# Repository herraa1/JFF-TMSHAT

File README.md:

# JFF Computer with TMSHAT

This is an enhanced version of the [JFF Computer](https://github.com/konkotgit/JFF) by @Skoti, which enables the use of the TMS9928A or TMS9929A Video Display Processors (VDPs), in addition to the TMS9918A VDP.

## Current Status

:white_check_mark: Completed!

The modified JFF mainboard 1.1b-TMSHAT Build1 has been successfully designed, built and tested (as of Aug 20th, 2025). See *warning* on the next paragraph.

The TMSRGBCustom TMSHAT Build1 has been successfully designed, built and tested (as of Sep 11th, 2025). It has been successfully tested for RGB output on the modified JFF mainboard 1.1b-TMSHAT Build1 with both a TMS9929A NL (50Hz) and a TMS9928AN (60Hz).

The TMSRGBv2 TMSHAT Build1 has been successfully designed, built and tested (as of Oct 11th, 2025). It has been successfully tested for RGB output on the modified JFF mainboard 1.1b-TMSHAT Build1 with a TMS9928AN (60Hz) and a TMS9929A NL (50Hz).

> [!WARNING]
>
> While building the JFF mainboard it has been detected that the original JFF mainboard revision 1.1b has a bug in the general purpose IO ports schematic similar (but different) to [the bug that affected the Omega Home Computer prior to version 1.5](https://github.com/skiselev/omega/issues/56) which the modified JFF mainboard revision 1.1b-TMSHAT Build1 has *inherited*. The bug does not affect MSX joysticks, only IO devices which require output to the trigger pins are affected.
>
> For existing original JFF revision 1.1b mainboards (and for the modified JFF mainboard revision 1.1b-TMSHAT Build1), the [JFF joyfix board](https://github.com/herraa1/JFF-1.1-joyfix-board-v1) interposer board has been developed to fix the joystick circuit problem, and has been already validated (as of Oct 3rd, 2025).
>
> A [new revision 1.1c](https://github.com/konkotgit/JFF?tab=readme-ov-file#revisions) of the original JFF mainboard that fixes the joystick circuit bug has been published by @Skoti (as of Oct 6th, 2025) solving [Issue #3](https://github.com/konkotgit/JFF/issues/3).
>
> And the equivalent [JFF-TMSHAT Mainboard revision 1.1c-TMSHAT](https://github.com/herraa1/JFF-TMSHAT/tree/main/hardware/kicad/JFF-TMSHAT-Mainboard-Build1/jff_mainboard-1.1c-TMSHAT) has been released by @herraa1 (as of Oct 6th, 2025), but has not been built nor tested.
>

> [!NOTE]
>
> Everything stated here about revision 1.1b-TMSHAT is applicable to 1.1c-TMSHAT. The only difference between the two board revisions is the fix for the joystick circuit bug.

## Sponsorship

.

The fabrication of the *Build1* mainboard 1.1b-TMSHAT, Hat-TMSRGBv2 and Hat-TMSRGBCustom PCB prototypes has been kindly sponsored by [PCBWay](https://www.pcbway.com), a global quality-focused PCB manufacturer which provides [sponsorship](https://www.kicad.org/sponsors/sponsors/) for the [KiCad project](https://www.kicad.org) as well as many educational and [open source hardware](https://en.wikipedia.org/wiki/Open-source_hardware) projects.

KiCad is the open source [EDA](https://en.wikipedia.org/wiki/Electronic_design_automation) platform of choice used to design the hardware circuitry provided in the JFF-TMSHAT project.

## Motivation

The JFF Computer by @Skoti is a [MSX1 compatible computer](https://www.msx.org/wiki/MSX1) which uses the TMS9918A VDP which is part of the [TMS9918 family](https://en.wikipedia.org/wiki/TMS9918) of Video Display Processors from Texas Instruments.
The TMS9918A outputs a 60Hz composite NTSC video signal, and thus the JFF has a single RCA video output connector with a composite video signal.

The TMS9928A and TMS9929A VDPs, from the same family of Video Display Processors, output instead analog luminance (Y) and color difference (R-Y and B-Y) signals.
Except for the video output signals, the TMS9918A, TMS9928A and TMS9929A VDPs behave identically and have an almost identical pinout.

The difference in the pinout of the TMS9918A, TMS9928A and TMS9929A VDPs affects the following pins:

| **Pin Number** | **TMS9918A Name** | **TMS9918A Description**        | **TMS9928A/TMS9929A Name** | **TMS9928A/TMS9929A Description** |
| -------------- | ----------------- | ------------------------------- | -------------------------- | --------------------------------- |
| 35             | EXTVDP            | External VDP input              | B-Y                        | B-Y color difference output       |
| 36             | COMVID            | Composite video output          | Y                          | luminance/sync output             |
| 38             | CPUCLK            | VDP color burst frequency clock | R-Y                        | R-Y color difference output       |

Given that the JFF Computer does not use VDP pins 35 nor 38, and just uses pin 36 for composite video output, it should be relatively straightforward to allow the use of the TMS9928A or TMS9929A VDPs alternatively to the TMS9918A VDP.
Using the luminance and color difference signals provided by the TMS9928A or TMS9929A VDPs, an enhanced output video signal like RGB or component video can be generated for a better user experience.

## Proposed Changes

### Original JFF Computer mainboard (rev 1.1b)

### Modified JFF Computer mainboard (rev 1.1b-TMSHAT)

The JFF computer mainboard is modified as described here.

* A new audio/video header J13 is added to the JFF computer mainboard, which can be used to select between the TMS9918A or TMS9928A/TMS9929A VDPs, and to provide the required audio and video signals to an external companion card called TMSHAT which converts them into a specific audio/video output.

  The header provides access to the following signals:

  | **Pin Number** | **Name**   | **Type<br>(from JFF connector point of view)** | **Function**                                              |
  | -------------- | ---------- | ---------------------------------------------- | --------------------------------------------------------- |
  | 1              | GND        | Power                                          | Common ground                                             |
  | 2              | +5V        | Power                                          | 5V power rail                                             |
  | 3              | CPUCLK/R-Y | OUT                                            | direct signal from pin 38 of VDP                          |
  | 4              | EXTVDP/B-Y | OUT                                            | direct signal from pin 35 of VDP                          |
  | 5              | COMVID/Y   | OUT                                            | direct signal from pin 36 of VDP                          |
  | 6              | COMVID_OUT | IN                                             | connected to JFF mainboard composite video output circuit |
  | 7              | NC         |                                                | (reserved)                                                |
  | 8              | AUDIO      | OUT                                            | final mixed audio signal                                  |

  A total of 8 pins are used for the audio/video header, giving 1 extra pin for future use.

  Allowed VDP configurations:

  - *TMS9918A*

    To use a TMS9918A VDP, pins 5 (COMVID/Y) and 6 (COMVID_OUT) of J13, which use inverted colors in the silkscreen text, must be bridged and a TMS9918A must be installed in U6.
    In this configuration the modified JFF computer works identically as the original JFF computer with a TMS9918A and outputs a composite video signal on the motherboard video RCA connector.

  - *TMS9928A/TMS9929A*

    To use a TMS9928A or TMS9929A VDP, a companion TMSHAT card needs to be connected to J13 and a TMS9928A or TMS9929A VDP must be installed in U6.
    In this configuration the modified JFF computer will provide an audio and video output according to the capabilities of the TMSHAT card connected.
    
* A small clearance area is defined between the power barrel connector and the DIN8 cassette connector in the JFF computer mainboard.

  This allows to, as long as they fit, seamlessly place in that area the additional audio/video connectors provided by the TMSHAT cards.
  Note that the additional audio/video connectors are never part of the JFF computer mainboard, they are instead soldered to the TMSHAT cards. But, for convenience, the mentioned area allows making such connectors available on the back of the JFF computer as if they were on the mainboard.

  The power led is relocated next to the Audio connector in the JFF computer motherboard to allow the described clearance.

* Enough clearance is preserved too for the DD1718PA +12V/-12V voltage module converter to be installed upside-down in the J5 header.

* A new extra 3mm hole is added to the JFF computer mainboard.

  A TMSHAT card must be properly attached to the JFF computer mainboard, specially as it has to deal with cable insertion/removal forces when audio/video connectors are present on the TMSHAT card itself.

  The top-left 3mm hole and the new 3mm hole on the JFF computer mainboard are the mechanical attachment points for the TMSHAT cards, while the audio/video header attachment provides the electrical signals.

* External companion TMSHAT cards are designed to be connected to the new audio/video header J13, attached to the previously described mainboard holes and shaped to avoid any collision with existing components in the JFF computer. The TMSHAT cards provide a specific audio/video output using one or more embedded connectors in the card itself.

  As an example, a pair of TMSHAT card implementations are provided to convert the luminance and color difference signals of the TMS9928A and TMS9929A VDPs to RGB, and output both the audio and RGB video signals through a DIN8 connector compatible with [audio/video cables for Panasonic MSX2+ machines](https://www.msx.org/wiki/RGB_(8-pin_DIN_45326)#Mitsubishi_.28Japan.29.2C_National.2FPanasonic_.28except_the_FS-A1WSX.29.2C_Sakhr.2C_Sony_and_Yamaha_computers_.2B_Sanyo_MSX2.2F2.2B_computers).

## [Hardware](hardware/kicad/)

This project provides source files for the following hardware designs:

* JFF mainboard revisions 1.1b-TMSHAT and 1.1c-TMSHAT aka [JFF-TMSHAT-Mainboard](#jff-tmshat-mainboard)

* TMSHAT for RGB output using a standard TMS-RGBv2 module, aka [JFF-TMSHAT-Hat-TMSRGBv2](#jff-tmshat-hat-tmsrgbv2)

* TMSHAT for RGB output using a custom TMS-RGB implementation, aka [JFF-TMSHAT-Hat-TMSRGBCustom](#jff-tmshat-hat-tmsrgbcustom)

### JFF-TMSHAT-Mainboard

This mainboard design allows using a TMS9928A or TMS9929A VDP in combination with a TMSHAT, or a TMS9918A VDP by just closing a jumper.

#### [JFF-TMSHAT-Mainboard Build1](hardware/kicad/JFF-TMSHAT-Mainboard-Build1/)

:white_check_mark: Revision 1.1b-TMSHAT of this board has been successfully built and tested.

* [Bill Of Materials (BoM)](https://html-preview.github.io/?url=https://raw.githubusercontent.com/herraa1/JFF-TMSHAT/main/hardware/kicad/JFF-TMSHAT-Mainboard-Build1/jff_mainboard-1.1b-TMSHAT/bom/ibom.html)

* [Schematic and PCB](https://kicanvas.org/?github=https%3A%2F%2Fgithub.com%2Fherraa1%2FJFF-TMSHAT%2Ftree%2Fmain%2Fhardware%2Fkicad%2FJFF-TMSHAT-Mainboard-Build1%2Fjff_mainboard-1.1b-TMSHAT)

|||
|-|-|
|JFF mainboard 1.1b-TMSHAT Build1<br>PCB unpopulated top|JFF mainboard 1.1b-TMSHAT Build1<br>PCB unpopulated bottom|

||
|:--|
|JFF mainboard 1.1b-TMSHAT Build1 PCB populated top,<br>with a TMSRGBCustom TMSHAT Build1 connected|

##### Configuration Options

This section provides visual details on how to configure the JFF mainboard 1.1b-TMSHAT for different VDPs.

###### Using a TMS9918A VDP

* Insert a TMS9918ANL into U6
* Use a jumper to bridge pins 5 and 6 of J13
* Connect a composite display to the RCA video connector of the JFF mainboard

###### Using a TMS9928A/TMS9929A VDP with the TMSRGB TMSHATs

* Insert a TMS9928AN/TMS9929ANL into U6
* Remove all jumpers from J13, if any
* Install two 20mm long vertical aluminum round posts on the JFF mainboard holes dedicated for TMSHATs

* Insert the TMSHAT by connecting it to the J13 header and using two M3 screws to secure it to the vertical round posts.

* Connect a 15KHz RGBS display (or a 15KHz video converter suitable for your modern display, like the [OSSC](https://junkerhq.net/xrgb/index.php/OSSC)) to the [Panasonic-compatible DIN8 video connector](https://www.msx.org/wiki/RGB_(8-pin_DIN_45326)#Mitsubishi_.28Japan.29.2C_National.2FPanasonic_.28except_the_FS-A1WSX.29.2C_Sakhr.2C_Sony_and_Yamaha_computers_.2B_Sanyo_MSX2.2F2.2B_computers) of the TMSHAT

  |||
  |-|-|
  |TMS9929A (50Hz) with a TMSRGBCustom TMSHAT|TMS9928A (60Hz) with a TMSRGBCustom TMSHAT|

### JFF-TMSHAT-Hat-TMSRGBv2

This TMSHAT provides RGB output via a DIN8 connector compatible with audio/video cables for Panasonic MSX2+ machines when using a TMS9928A or TMS9929A VDP.

It requires a [TMS-RGB v2 module](https://tms-rgb.com/) by [Nicholas Piegdon](https://twitter.com/npiegdon).

#### [JFF-TMSHAT-Hat-TMSRGBv2 Build1](hardware/kicad/JFF-TMSHAT-Hat-TMSRGBv2-Build1/)

:white_check_mark: This board has been successfully built and tested.

[Bill Of Materials (BoM)](https://html-preview.github.io/?url=https://raw.githubusercontent.com/herraa1/JFF-TMSHAT/main/hardware/kicad/JFF-TMSHAT-Hat-TMSRGBv2-Build1/bom/ibom.html)

[Schematic and PCB](https://kicanvas.org/?github=https%3A%2F%2Fgithub.com%2Fherraa1%2FJFF-TMSHAT%2Ftree%2Fmain%2Fhardware%2Fkicad%2FJFF-TMSHAT-Hat-TMSRGBv2-Build1)

|||
|-|-|
|TMSRGBv2 TMSHAT Build1<br>PCB unpopulated top|TMSRGBv2 TMSHAT Build1<br>PCB unpopulated bottom|

||
|:--|
|TMSRGBv2 TMSHAT Build1 PCB populated top with TMSRGBv2 connected|

||
|:--|
|TMSRGBv2 TMSHAT Build1 PCB populated bottom with TMSRGBv2 connected|

### JFF-TMSHAT-Hat-TMSRGBCustom

This TMSHAT provides RGB output via a DIN8 connector compatible with audio/video cables for Panasonic MSX2+ machines when using a TMS9928A or TMS9929A VDP.

It implements a custom TMS-RGB directly in the TMSHAT.

#### [JFF-TMSHAT-Hat-TMSRGBCustom-Build1](hardware/kicad/JFF-TMSHAT-Hat-TMSRGBCustom-Build1/)

:white_check_mark: This board has been successfully built and tested.

[Bill Of Materials (BoM)](https://html-preview.github.io/?url=https://raw.githubusercontent.com/herraa1/JFF-TMSHAT/main/hardware/kicad/JFF-TMSHAT-Hat-TMSRGBCustom-Build1/bom/ibom.html)

[Schematic and PCB](https://kicanvas.org/?github=https%3A%2F%2Fgithub.com%2Fherraa1%2FJFF-TMSHAT%2Ftree%2Fmain%2Fhardware%2Fkicad%2FJFF-TMSHAT-Hat-TMSRGBCustom-Build1)

|
|-|-|
|TMSRGBCustom TMSHAT Build1<br>PCB unpopulated top|TMSRGBCustom TMSHAT Build1<br>PCB unpopulated bottom|

||
|:--|
|TMSRGBCustom TMSHAT Build1 PCB populated top|

||
|:--|
|TMSRGBCustom TMSHAT Build1 PCB populated bottom (I)|

|
|-|-|
|TMSRGBCustom TMSHAT Build1<br>PCB populated bottom (II)|TMSRGBCustom TMSHAT Build1<br>PCB populated bottom (III)|

## Compatibility tests

| **Motherboard**          | **VDP**     | **TMSHAT**          | **Video Output** | **Result**     |
| ------------------------ | ----------- | ------------------- | ---------------- | -------------- |
| rev 1.1b-TMSHAT Build1   | TMS9918ANL  | None (bridge 5&6)   | Composite 60Hz   | OK             |
| rev 1.1b-TMSHAT Build1   | TMS9928AN   | TMSRGBCustom Build1 | RGBS 60Hz        | OK             |
| rev 1.1b-TMSHAT Build1   | TMS9929ANL  | TMSRGBCustom Build1 | RGBS 50Hz        | OK             |
| rev 1.1b-TMSHAT Build1   | TMS9928AN   | TMSRGBv2 Build1     | RGBS 60Hz        | OK             |
| rev 1.1b-TMSHAT Build1   | TMS9929ANL  | TMSRGBv2 Build1     | RGBS 50Hz        | OK             |

## Design considerations

* The external connectors in the mainboard of the original JFF computer must not be relocated
* Modifications to the original JFF computer must be kept to the minimum necessary to achieve the functional goals
* The modified JFF-TMSHAT computer must behave exactly as the original JFF computer when configured in TMS9918A mode
* A TMSHAT card must not collide with components of the JFF computer nor with the DD1718PA voltage converter module

## Random notes (for internal reference only)

* The female header of the TMSHAT card must use long enough pins to account for the height of the connector used in the TMSHAT
* A minimum of 20mm of separation is required between the mainboard PCB and the TMSHAT PCB in order to use an inverted DIN8 connector in the TMSHAT card

## References

Skoti's JFF Computer
* https://github.com/konkotgit/JFF

## Image Sources

* https://www.oshwa.org/open-source-hardware-logo/

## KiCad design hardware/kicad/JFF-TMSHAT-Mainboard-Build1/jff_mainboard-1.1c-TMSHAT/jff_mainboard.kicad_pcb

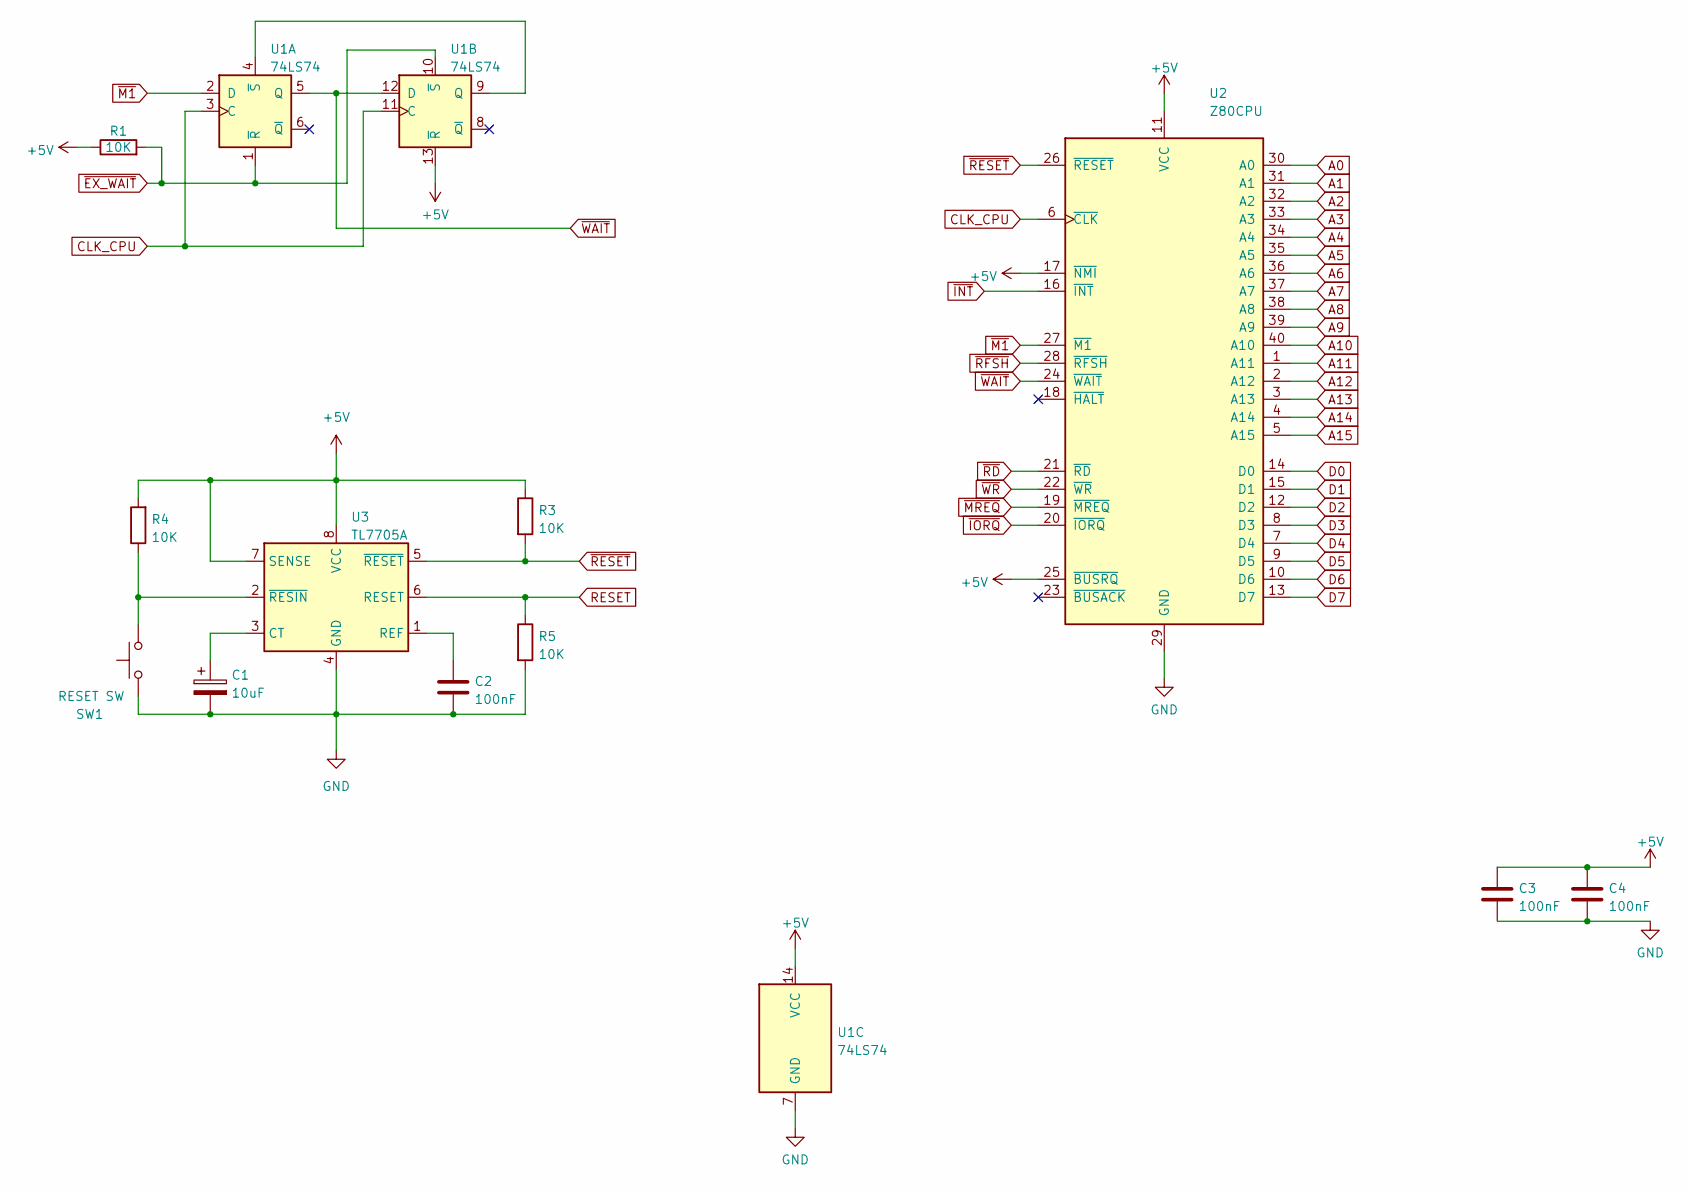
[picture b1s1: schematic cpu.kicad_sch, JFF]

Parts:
C1: 10uF; CP_Radial_D5.0mm_P2.50mm
C2, C3, C4: 100nF; C_Disc_D3.0mm_W2.0mm_P2.50mm
R1, R3, R4, R5: 10K; R_Axial_DIN0204_L3.6mm_D1.6mm_P7.62mm_Horizontal
SW1: RESET SW; SW_Tactile_SPST_Angled_PTS645Vx83-2LFS
U1: 74LS74; DIP-14_W7.62mm_Socket
U2: Z80CPU; DIP-40_W15.24mm_Socket
U3: TL7705A; DIP-8_W7.62mm_Socket

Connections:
+5V: C3.1, C4.1, R1.1, R3.1, R4.2, U1.13 (~R), U1.14 (VCC), U2.11 (VCC), U2.17 (~NMI), U2.25 (~BUSRQ), U3.7 (SENSE), U3.8 (VCC); also elsewhere on the board
A0: U2.30 (A0); also elsewhere on the board
A1: U2.31 (A1); also elsewhere on the board
A2: U2.32 (A2); also elsewhere on the board
A3: U2.33 (A3); also elsewhere on the board
A4: U2.34 (A4); also elsewhere on the board
A5: U2.35 (A5); also elsewhere on the board
A6: U2.36 (A6); also elsewhere on the board
A7: U2.37 (A7); also elsewhere on the board
A8: U2.38 (A8); also elsewhere on the board
A9: U2.39 (A9); also elsewhere on the board
A10: U2.40 (A10); also elsewhere on the board
A11: U2.1 (A11); also elsewhere on the board
A12: U2.2 (A12); also elsewhere on the board
A13: U2.3 (A13); also elsewhere on the board
A14: U2.4 (A14); also elsewhere on the board
A15: U2.5 (A15); also elsewhere on the board
CLK_CPU: U1.3 (C), U1.11 (C), U2.6 (~CLK); also elsewhere on the board
D0: U2.14 (D0); also elsewhere on the board
D1: U2.15 (D1); also elsewhere on the board
D2: U2.12 (D2); also elsewhere on the board
D3: U2.8 (D3); also elsewhere on the board
D4: U2.7 (D4); also elsewhere on the board
D5: U2.9 (D5); also elsewhere on the board
D6: U2.10 (D6); also elsewhere on the board
D7: U2.13 (D7); also elsewhere on the board
GND: C1.2, C2.2, C3.2, C4.2, R5.2, SW1.1, U1.7 (GND), U2.29 (GND), U3.4 (GND); also elsewhere on the board
unnamed: U1.4 (~S), U1.9 (Q)
unnamed: C1.1, U3.3 (CT)
unnamed: C2.1, U3.1 (REF)
unnamed: R4.1, SW1.2, U3.2 (~RESIN)
RESET: R5.1, U3.6 (RESET); also elsewhere on the board
~EX_WAIT: R1.2, U1.1 (~R), U1.10 (~S); also elsewhere on the board
~INT: U2.16 (~INT); also elsewhere on the board
~IORQ: U2.20 (~IORQ); also elsewhere on the board
~M1: U1.2 (D), U2.27 (~M1); also elsewhere on the board
~MREQ: U2.19 (~MREQ); also elsewhere on the board
~RD: U2.21 (~RD); also elsewhere on the board
~RESET: R3.2, U2.26 (~RESET), U3.5 (~RESET); also elsewhere on the board
~RFSH: U2.28 (~RFSH); also elsewhere on the board
~WAIT: U1.5 (Q), U1.12 (D), U2.24 (~WAIT)
~WR: U2.22 (~WR); also elsewhere on the board

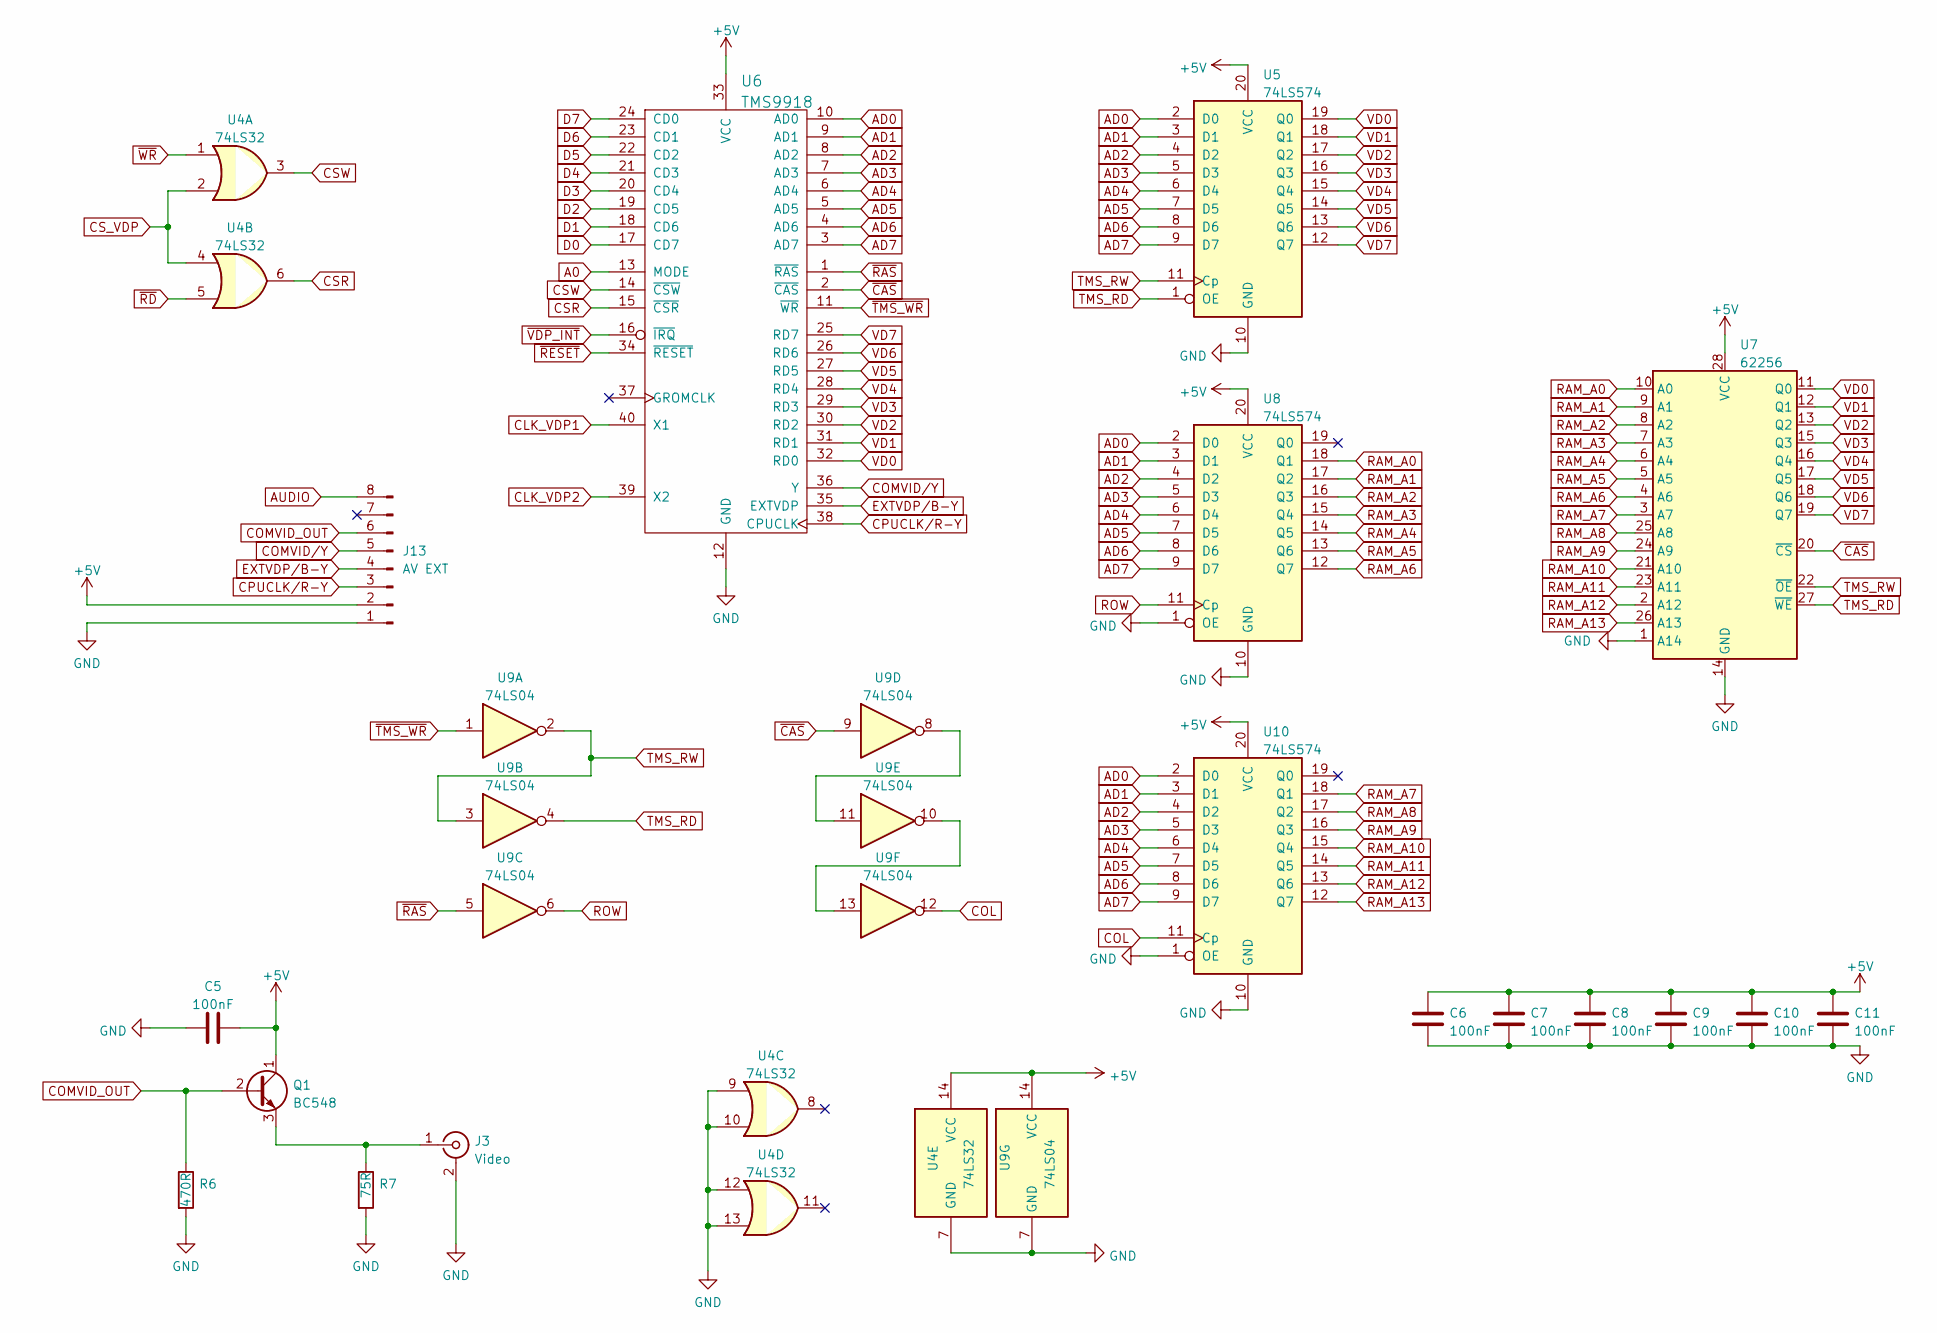
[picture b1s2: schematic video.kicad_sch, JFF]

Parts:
C5, C6, C7, C8, C9, C10, C11: 100nF; C_Disc_D3.0mm_W2.0mm_P2.50mm
J3: Video; Conn_RCA_Right
J13: AV EXT; PinHeader_1x08_P2.54mm_Vertical
Q1: BC548; TO-92_Inline
R6: 470R; R_Axial_DIN0204_L3.6mm_D1.6mm_P7.62mm_Horizontal
R7: 75R; R_Axial_DIN0204_L3.6mm_D1.6mm_P7.62mm_Horizontal
U4: 74LS32; DIP-14_W7.62mm_Socket
U5, U8, U10: 74LS574; DIP-20_W7.62mm_Socket
U6: TMS9918; DIP-40_W15.24mm_Socket
U7: 62256; DIP-28_W15.24mm_Socket
U9: 74LS04; DIP-14_W7.62mm_Socket

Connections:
+5V: C5.2, C6.1, C7.1, C8.1, C9.1, C10.1, C11.1, J13.2, Q1.1 (C), U4.14 (VCC), U5.20 (VCC), U6.33 (VCC), U7.28 (VCC), U8.20 (VCC), U9.14 (VCC), U10.20 (VCC); also elsewhere on the board
A0: U6.13 (MODE); also elsewhere on the board
AD0: U5.2 (D0), U6.10 (AD0), U8.2 (D0), U10.2 (D0)
AD1: U5.3 (D1), U6.9 (AD1), U8.3 (D1), U10.3 (D1)
AD2: U5.4 (D2), U6.8 (AD2), U8.4 (D2), U10.4 (D2)
AD3: U5.5 (D3), U6.7 (AD3), U8.5 (D3), U10.5 (D3)
AD4: U5.6 (D4), U6.6 (AD4), U8.6 (D4), U10.6 (D4)
AD5: U5.7 (D5), U6.5 (AD5), U8.7 (D5), U10.7 (D5)
AD6: U5.8 (D6), U6.4 (AD6), U8.8 (D6), U10.8 (D6)
AD7: U5.9 (D7), U6.3 (AD7), U8.9 (D7), U10.9 (D7)
AUDIO: J13.8; also elsewhere on the board
CLK_VDP1: U6.40 (X1); also elsewhere on the board
CLK_VDP2: U6.39 (X2); also elsewhere on the board
COL: U9.12, U10.11 (Cp)
COMVID_OUT: J13.6, Q1.2 (B), R6.1
COMVID/Y: J13.5, U6.36 (Y)
CPUCLK/R-Y: J13.3, U6.38 (CPUCLK)
CSR: U4.6, U6.15 (~CSR)
CSW: U4.3, U6.14 (~CSW)
CS_VDP: U4.2, U4.4; also elsewhere on the board
D0: U6.17 (CD7); also elsewhere on the board
D1: U6.18 (CD6); also elsewhere on the board
D2: U6.19 (CD5); also elsewhere on the board
D3: U6.20 (CD4); also elsewhere on the board
D4: U6.21 (CD3); also elsewhere on the board
D5: U6.22 (CD2); also elsewhere on the board
D6: U6.23 (CD1); also elsewhere on the board
D7: U6.24 (CD0); also elsewhere on the board
EXTVDP/B-Y: J13.4, U6.35 (EXTVDP)
GND: C5.1, C6.2, C7.2, C8.2, C9.2, C10.2, C11.2, J3.2 (Ext), J13.1, R6.2, R7.2, U4.7 (GND), U4.9, U4.10, U4.12, U4.13, U5.10 (GND), U6.12 (GND), U7.1 (A14), U7.14 (GND), U8.1 (OE), U8.10 (GND), U9.7 (GND), U10.1 (OE), U10.10 (GND); also elsewhere on the board
unnamed: J3.1 (In), Q1.3 (E), R7.1
unnamed: U9.10, U9.13
unnamed: U9.8, U9.11
RAM_A0: U7.10 (A0), U8.18 (Q1)
RAM_A1: U7.9 (A1), U8.17 (Q2)
RAM_A2: U7.8 (A2), U8.16 (Q3)
RAM_A3: U7.7 (A3), U8.15 (Q4)
RAM_A4: U7.6 (A4), U8.14 (Q5)
RAM_A5: U7.5 (A5), U8.13 (Q6)
RAM_A6: U7.4 (A6), U8.12 (Q7)
RAM_A7: U7.3 (A7), U10.18 (Q1)
RAM_A8: U7.25 (A8), U10.17 (Q2)
RAM_A9: U7.24 (A9), U10.16 (Q3)
RAM_A10: U7.21 (A10), U10.15 (Q4)
RAM_A11: U7.23 (A11), U10.14 (Q5)
RAM_A12: U7.2 (A12), U10.13 (Q6)
RAM_A13: U7.26 (A13), U10.12 (Q7)
ROW: U8.11 (Cp), U9.6
TMS_RD: U5.1 (OE), U7.27 (~WE), U9.4
TMS_RW: U5.11 (Cp), U7.22 (~OE), U9.2, U9.3
VD0: U5.19 (Q0), U6.32 (RD0), U7.11 (Q0)
VD1: U5.18 (Q1), U6.31 (RD1), U7.12 (Q1)
VD2: U5.17 (Q2), U6.30 (RD2), U7.13 (Q2)
VD3: U5.16 (Q3), U6.29 (RD3), U7.15 (Q3)
VD4: U5.15 (Q4), U6.28 (RD4), U7.16 (Q4)
VD5: U5.14 (Q5), U6.27 (RD5), U7.17 (Q5)
VD6: U5.13 (Q6), U6.26 (RD6), U7.18 (Q6)
VD7: U5.12 (Q7), U6.25 (RD7), U7.19 (Q7)
~CAS: U6.2 (~CAS), U7.20 (~CS), U9.9
~RAS: U6.1 (~RAS), U9.5
~RD: U4.5; also elsewhere on the board
~RESET: U6.34 (~RESET); also elsewhere on the board
~TMS_WR: U6.11 (~WR), U9.1
~VDP_INT: U6.16 (~IRQ); also elsewhere on the board
~WR: U4.1; also elsewhere on the board

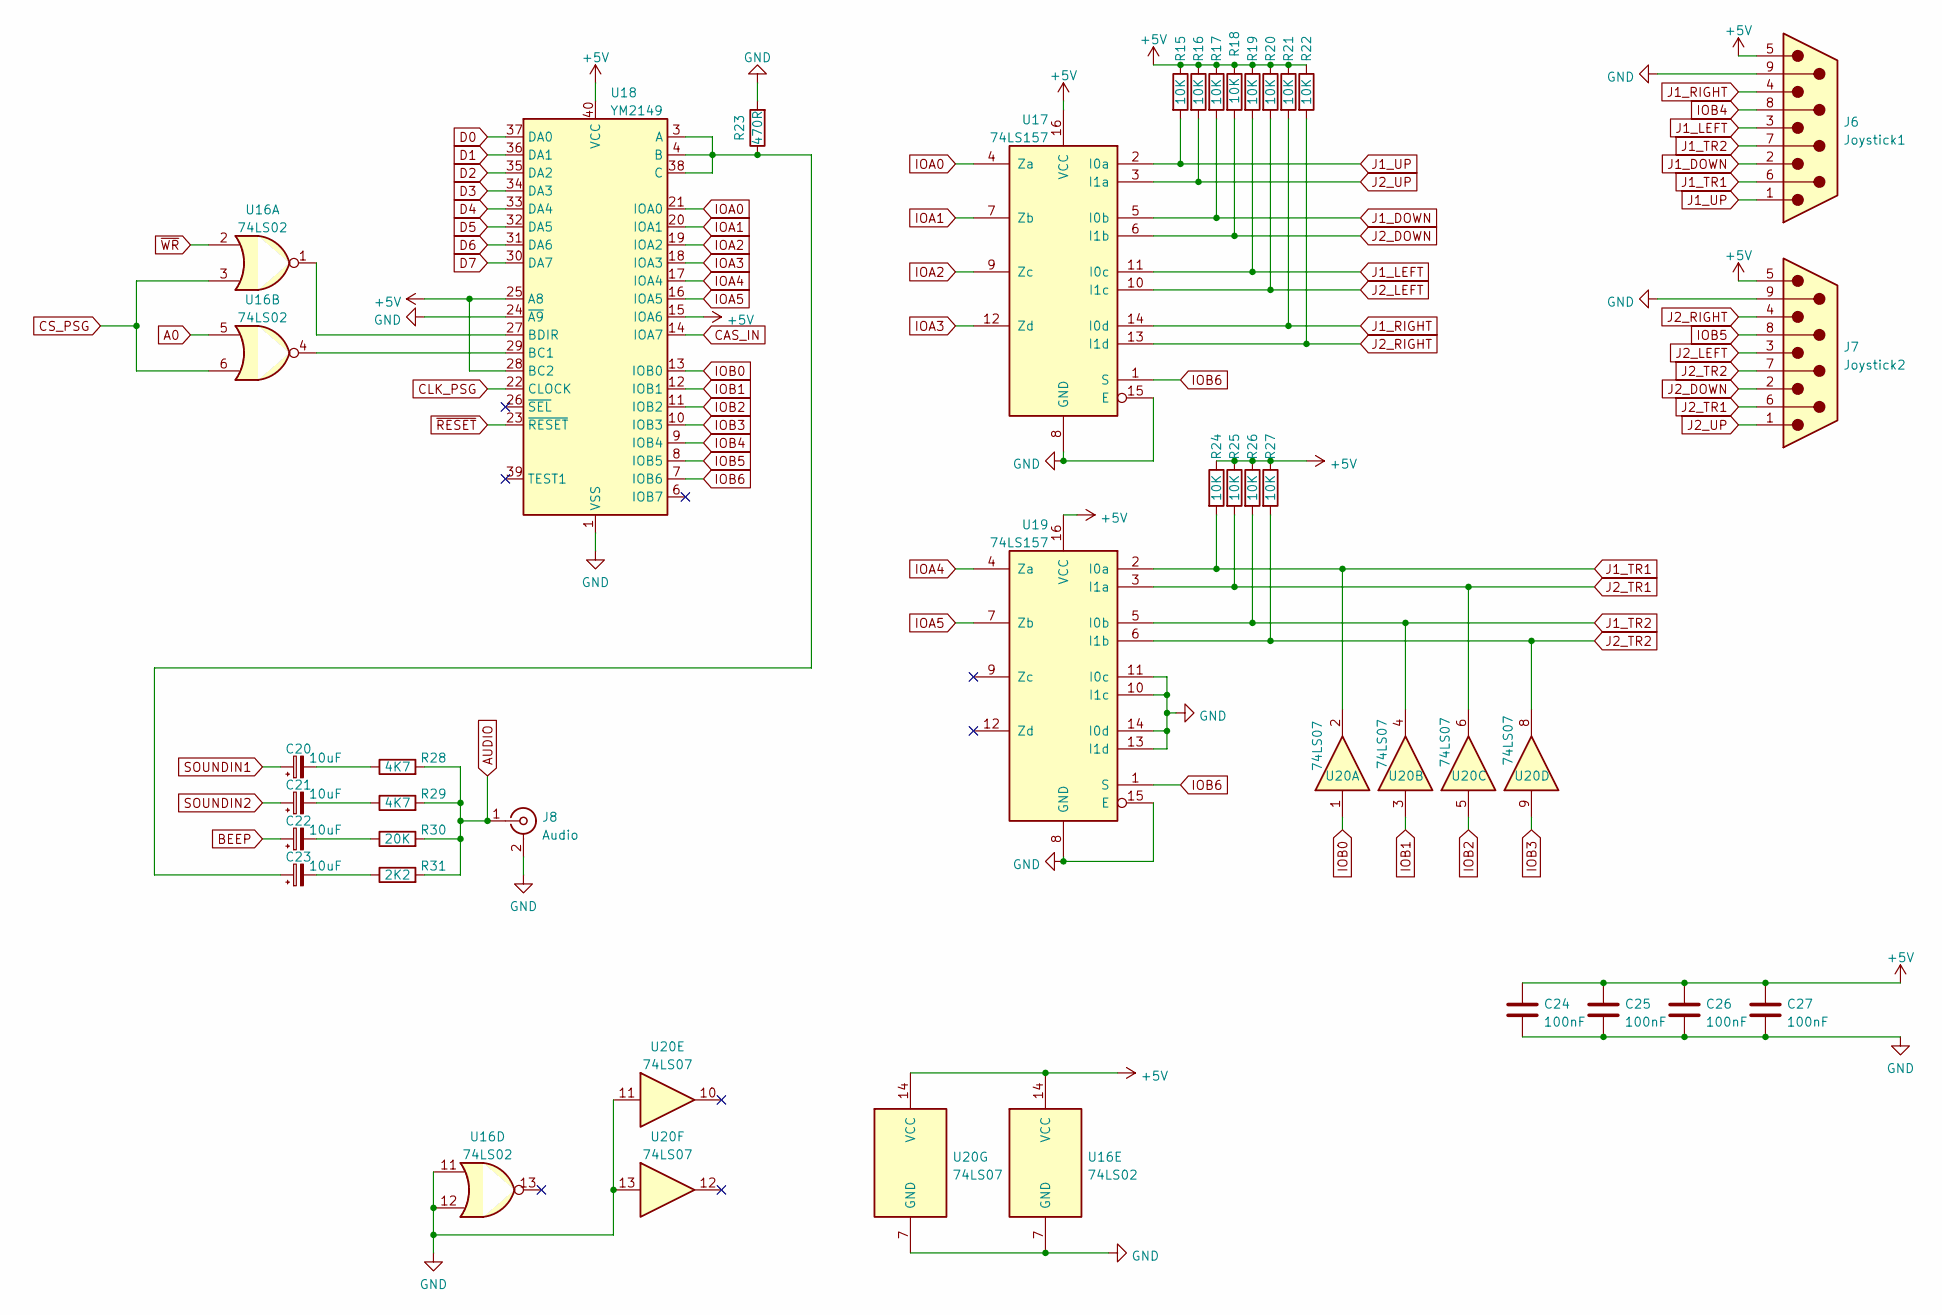
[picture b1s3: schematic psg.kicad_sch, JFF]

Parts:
C20, C21, C22, C23: 10uF; CP_Radial_D5.0mm_P2.50mm
C24, C25, C26, C27: 100nF; C_Disc_D3.0mm_W2.0mm_P2.50mm
J6: Joystick1; Conn_Dsub_DE9M
J7: Joystick2; Conn_Dsub_DE9M
J8: Audio; Conn_RCA_Right
R15, R16, R17, R18, R19, R20, R21, R22, R24, R25, R26, R27: 10K; R_Axial_DIN0204_L3.6mm_D1.6mm_P7.62mm_Horizontal
R23: 470R; R_Axial_DIN0204_L3.6mm_D1.6mm_P7.62mm_Horizontal
R28, R29: 4K7; R_Axial_DIN0204_L3.6mm_D1.6mm_P7.62mm_Horizontal
R30: 20K; R_Axial_DIN0204_L3.6mm_D1.6mm_P7.62mm_Horizontal
R31: 2K2; R_Axial_DIN0204_L3.6mm_D1.6mm_P7.62mm_Horizontal
U16: 74LS02; DIP-14_W7.62mm_Socket
U17, U19: 74LS157; DIP-16_W7.62mm_Socket
U18: YM2149; DIP-40_W15.24mm_Socket
U20: 74LS07; DIP-14_W7.62mm_Socket

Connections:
+5V: C24.1, C25.1, C26.1, C27.1, J6.5, J7.5, R15.1, R16.1, R17.1, R18.1, R19.1, R20.1, R21.1, R22.1, R24.1, R25.1, R26.1, R27.1, U16.14 (VCC), U17.16 (VCC), U18.15 (IOA6), U18.25 (A8), U18.28 (BC2), U18.40 (VCC), U19.16 (VCC), U20.14 (VCC); also elsewhere on the board
A0: U16.5; also elsewhere on the board
AUDIO: J8.1 (In), R28.2, R29.2, R30.2, R31.2; also elsewhere on the board
BEEP: C22.1; also elsewhere on the board
CAS_IN: U18.14 (IOA7); also elsewhere on the board
CLK_PSG: U18.22 (CLOCK); also elsewhere on the board
CS_PSG: U16.3, U16.6; also elsewhere on the board
D0: U18.37 (DA0); also elsewhere on the board
D1: U18.36 (DA1); also elsewhere on the board
D2: U18.35 (DA2); also elsewhere on the board
D3: U18.34 (DA3); also elsewhere on the board
D4: U18.33 (DA4); also elsewhere on the board
D5: U18.32 (DA5); also elsewhere on the board
D6: U18.31 (DA6); also elsewhere on the board
D7: U18.30 (DA7); also elsewhere on the board
GND: C24.2, C25.2, C26.2, C27.2, J6.9, J7.9, J8.2 (Ext), R23.2, U16.7 (GND), U16.11, U16.12, U17.8 (GND), U17.15 (E), U18.1 (VSS), U18.24 (~A9), U19.8 (GND), U19.10 (I1c), U19.11 (I0c), U19.13 (I1d), U19.14 (I0d), U19.15 (E), U20.7 (GND), U20.11, U20.13; also elsewhere on the board
IOA0: U17.4 (Za), U18.21 (IOA0)
IOA1: U17.7 (Zb), U18.20 (IOA1)
IOA2: U17.9 (Zc), U18.19 (IOA2)
IOA3: U17.12 (Zd), U18.18 (IOA3)
IOA4: U18.17 (IOA4), U19.4 (Za)
IOA5: U18.16 (IOA5), U19.7 (Zb)
IOB0: U18.13 (IOB0), U20.1
IOB1: U18.12 (IOB1), U20.3
IOB2: U18.11 (IOB2), U20.5
IOB3: U18.10 (IOB3), U20.9
IOB4: J6.8, U18.9 (IOB4)
IOB5: J7.8, U18.8 (IOB5)
IOB6: U17.1 (S), U18.7 (IOB6), U19.1 (S)
J1_DOWN: J6.2, R17.2, U17.5 (I0b)
J1_LEFT: J6.3, R19.2, U17.11 (I0c)
J1_RIGHT: J6.4, R21.2, U17.14 (I0d)
J1_TR1: J6.6, R24.2, U19.2 (I0a), U20.2
J1_TR2: J6.7, R26.2, U19.5 (I0b), U20.4
J1_UP: J6.1, R15.2, U17.2 (I0a)
J2_DOWN: J7.2, R18.2, U17.6 (I1b)
J2_LEFT: J7.3, R20.2, U17.10 (I1c)
J2_RIGHT: J7.4, R22.2, U17.13 (I1d)
J2_TR1: J7.6, R25.2, U19.3 (I1a), U20.6
J2_TR2: J7.7, R27.2, U19.6 (I1b), U20.8
J2_UP: J7.1, R16.2, U17.3 (I1a)
unnamed: C20.2, R28.1
unnamed: C21.2, R29.1
unnamed: C22.2, R30.1
unnamed: C23.2, R31.1
unnamed: C23.1, R23.1, U18.3 (A), U18.4 (B), U18.38 (C)
unnamed: U16.4, U18.29 (BC1)
unnamed: U16.1, U18.27 (BDIR)
SOUNDIN1: C20.1; also elsewhere on the board
SOUNDIN2: C21.1; also elsewhere on the board
~RESET: U18.23 (~RESET); also elsewhere on the board
~WR: U16.2; also elsewhere on the board

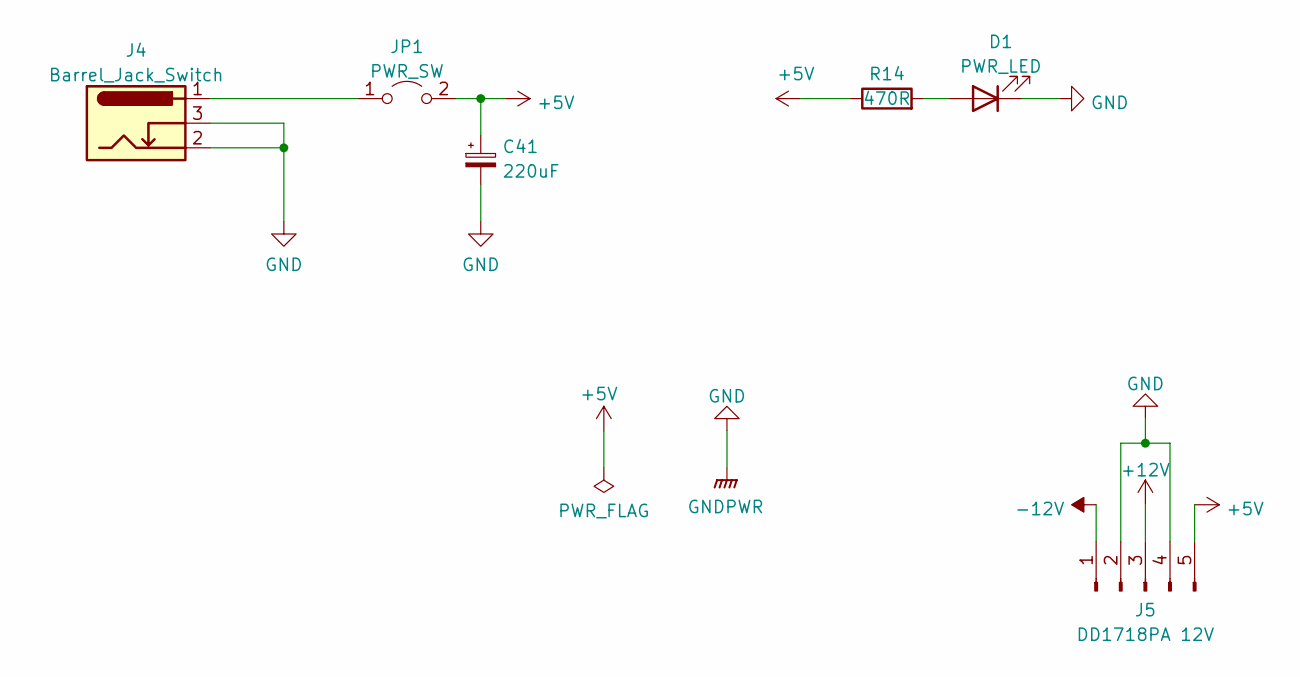
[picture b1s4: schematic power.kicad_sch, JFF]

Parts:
C41: 220uF; CP_Radial_D5.0mm_P2.50mm
D1: PWR_LED; LED_D3.0mm
J4: Barrel_Jack_Switch; BarrelJack_Horizontal
J5: DD1718PA 12V; PinHeader_1x05_P2.54mm_Vertical
JP1: PWR_SW; PinHeader_1x02_P2.54mm_Vertical
R14: 470R; R_Axial_DIN0204_L3.6mm_D1.6mm_P7.62mm_Horizontal

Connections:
+5V: C41.1, J5.5, JP1.2 (B), R14.1; also elsewhere on the board
+12V: J5.3; also elsewhere on the board
-12V: J5.1; also elsewhere on the board
GND: C41.2, D1.1 (K), J4.2, J4.3, J5.2, J5.4; also elsewhere on the board
unnamed: D1.2 (A), R14.2
unnamed: J4.1, JP1.1 (A)

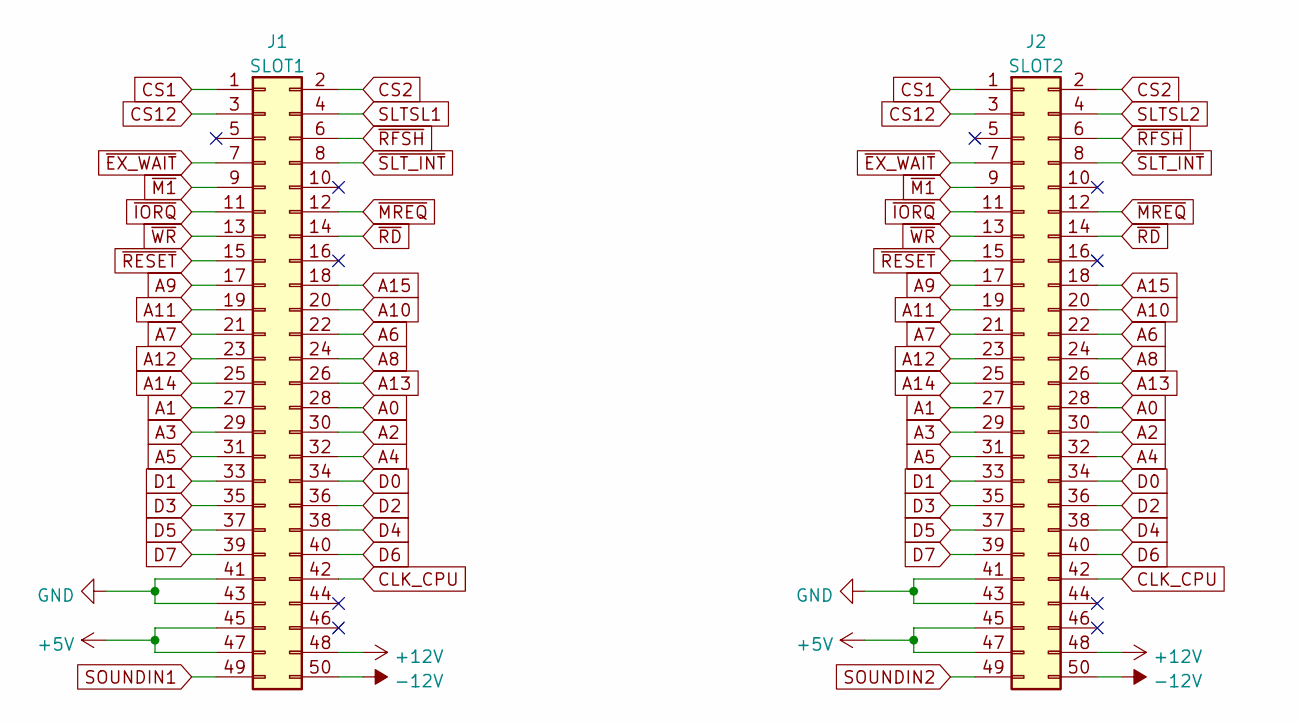
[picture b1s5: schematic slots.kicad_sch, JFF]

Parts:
J1: SLOT1; Conn_Edge_50P
J2: SLOT2; Conn_Edge_50P

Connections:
+5V: J1.45, J1.47, J2.45, J2.47; also elsewhere on the board
+12V: J1.48, J2.48; also elsewhere on the board
-12V: J1.50, J2.50; also elsewhere on the board
A0: J1.28, J2.28; also elsewhere on the board
A1: J1.27, J2.27; also elsewhere on the board
A2: J1.30, J2.30; also elsewhere on the board
A3: J1.29, J2.29; also elsewhere on the board
A4: J1.32, J2.32; also elsewhere on the board
A5: J1.31, J2.31; also elsewhere on the board
A6: J1.22, J2.22; also elsewhere on the board
A7: J1.21, J2.21; also elsewhere on the board
A8: J1.24, J2.24; also elsewhere on the board
A9: J1.17, J2.17; also elsewhere on the board
A10: J1.20, J2.20; also elsewhere on the board
A11: J1.19, J2.19; also elsewhere on the board
A12: J1.23, J2.23; also elsewhere on the board
A13: J1.26, J2.26; also elsewhere on the board
A14: J1.25, J2.25; also elsewhere on the board
A15: J1.18, J2.18; also elsewhere on the board
CLK_CPU: J1.42, J2.42; also elsewhere on the board
CS1: J1.1, J2.1; also elsewhere on the board
CS2: J1.2, J2.2; also elsewhere on the board
CS12: J1.3, J2.3; also elsewhere on the board
D0: J1.34, J2.34; also elsewhere on the board
D1: J1.33, J2.33; also elsewhere on the board
D2: J1.36, J2.36; also elsewhere on the board
D3: J1.35, J2.35; also elsewhere on the board
D4: J1.38, J2.38; also elsewhere on the board
D5: J1.37, J2.37; also elsewhere on the board
D6: J1.40, J2.40; also elsewhere on the board
D7: J1.39, J2.39; also elsewhere on the board
GND: J1.41, J1.43, J2.41, J2.43; also elsewhere on the board
SLTSL1: J1.4; also elsewhere on the board
SLTSL2: J2.4; also elsewhere on the board
SOUNDIN1: J1.49; also elsewhere on the board
SOUNDIN2: J2.49; also elsewhere on the board
~EX_WAIT: J1.7, J2.7; also elsewhere on the board
~IORQ: J1.11, J2.11; also elsewhere on the board
~M1: J1.9, J2.9; also elsewhere on the board
~MREQ: J1.12, J2.12; also elsewhere on the board
~RD: J1.14, J2.14; also elsewhere on the board
~RESET: J1.15, J2.15; also elsewhere on the board
~RFSH: J1.6, J2.6; also elsewhere on the board
~SLT_INT: J1.8, J2.8; also elsewhere on the board
~WR: J1.13, J2.13; also elsewhere on the board

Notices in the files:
hardware/kicad/JFF-TMSHAT-Hat-TMSRGBCustom-Build1/JFF-TMSHAT-Hat-TMSRGBCustom.kicad_pcb:
© 2025 Albert Herranz
